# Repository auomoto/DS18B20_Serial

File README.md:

# Read DS18B20 Sensors through a serial port
We read a string of DS18B20 1-Wire temperature sensors using a DS2480B serial-to-1-Wire line driver. Our board also uses a MAX233 RS-232 chip to interface with true RS-232.

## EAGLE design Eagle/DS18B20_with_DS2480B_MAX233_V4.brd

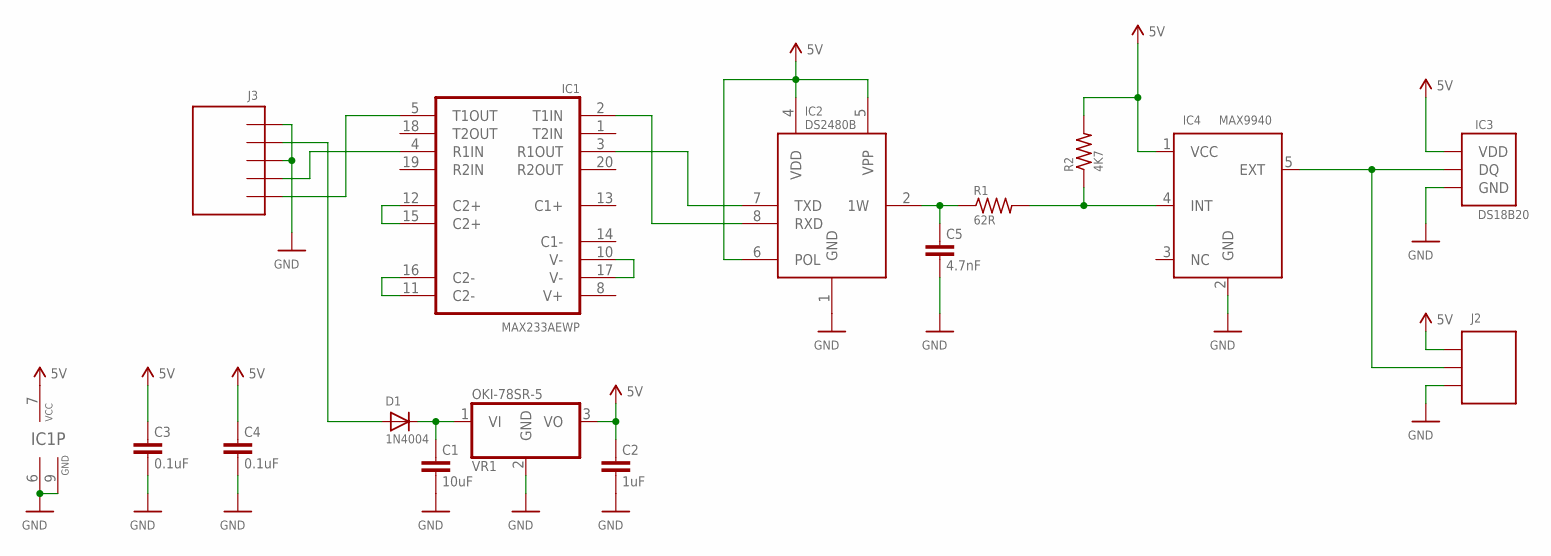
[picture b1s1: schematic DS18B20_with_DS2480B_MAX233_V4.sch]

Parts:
C1: 10uF; CAPC3225X270N
C2: 1uF; CAPC2013X135N
C3, C4: 0.1uF; CAPC2013X135N
C5: 4.7nF; CAPC2013X135N
D1: 1N4004; DO41-10
IC1: MAX233AEWP; SO20L
IC2: DS2480B; SO08
IC3: DS18B20; TO92-
IC4: MAX9940; SC70-5L
J2: DF1B-3P
J3: DF1B-5P
R1: 62R; RESISTOR-0805
R2: 4K7; RESISTOR-0805
VR1: OKI-78SR-5; OKI-78SR

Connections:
5V: C2.1, C3.1, C4.1, IC1.7 (VCC), IC2.4 (VDD), IC2.5 (VPP), IC2.6 (POL), IC3.3 (VDD), IC4.1 (VCC), J2.P$3, R2.2, VR1.3 (VO)
GND: C1.2, C2.2, C3.2, C4.2, C5.2, IC1.6 (GND), IC1.9 (GND), IC2.1 (GND), IC3.1 (GND), IC4.2 (GND), J2.P$1, J3.P$3, J3.P$5, VR1.2 (GND)
unnamed: D1.A, J3.P$4
unnamed: C1.1, D1.C, VR1.1 (VI)
unnamed: IC1.2 (T1IN), IC2.8 (RXD)
unnamed: IC1.5 (T1OUT), J3.P$1
unnamed: IC1.4 (R1IN), J3.P$2
unnamed: IC1.12 (C2+), IC1.15 (C2+)
unnamed: IC1.11 (C2-), IC1.16 (C2-)
unnamed: IC1.10 (V-), IC1.17 (V-)
unnamed: IC1.3 (R1OUT), IC2.7 (TXD)
unnamed: C5.1, IC2.2 (1W), R1.1
unnamed: IC4.4 (INT), R1.2, R2.1
unnamed: IC3.2 (DQ), IC4.5 (EXT), J2.P$2

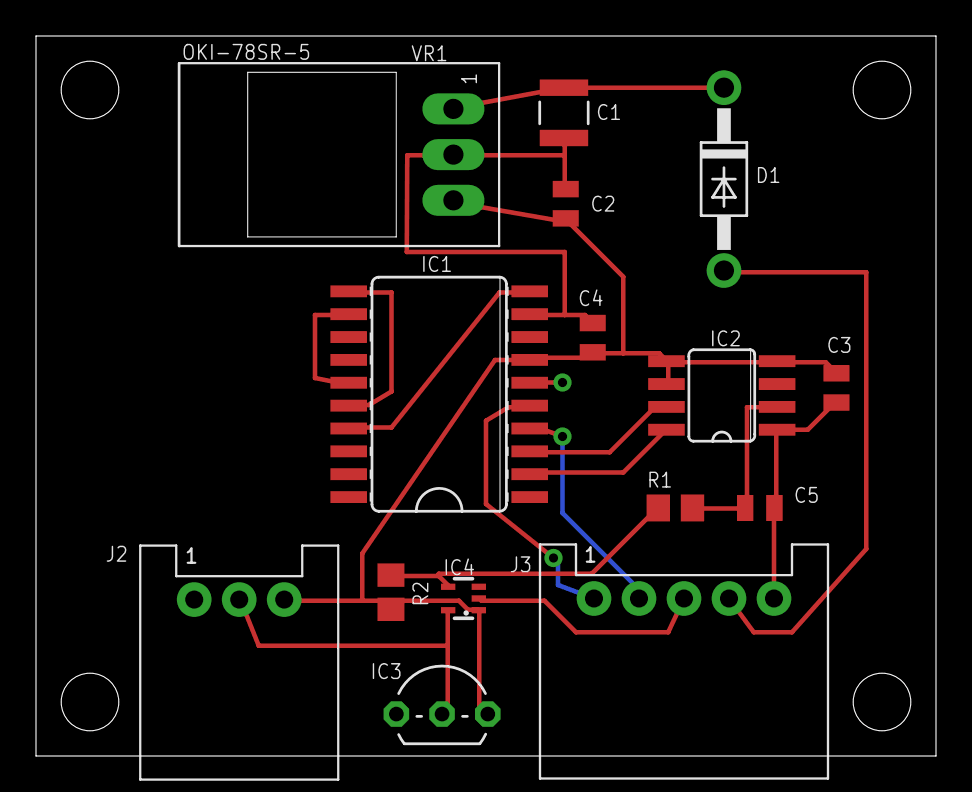
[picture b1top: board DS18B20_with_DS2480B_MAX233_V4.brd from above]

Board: 2 copper layers, 50.0 x 40.0 mm, 15 parts (0 on the bottom side), 14 nets.

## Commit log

2016-01-14 Added exe files
2016-01-14 Added swp files
2016-01-14 Minor edits (comments)
2016-01-20 Full rewrite
2016-01-20 Old version saved
2016-01-21 Fixed negative temperature readouts
2016-01-21 Added DS2480B mention
2016-01-21 Completely new board layout
2016-02-03 Started working on Search Rom
2016-02-03 Design with MAX9940 protection
2016-02-07 Added searchROM
2016-02-07 Some cleanup
2016-02-08 Fixed negative temperatures again
2016-02-09 Enabled flex speed
    Flex speed parameters were loaded but not used on the detect/response or
    search accelerator commands.
2016-02-11 Added -a (print addresses) option
